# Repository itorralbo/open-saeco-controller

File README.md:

# Open Saeco Controller

Controladora open-source para sustituir la electrónica de la Saeco Incanto HD8911,
placa objetivo 421941308981/01. Proyecto independiente, sin afiliación a Philips/Saeco.

**Rev A: diseño en curso, sin hardware fabricado ni ensayado. Hay 230 VAC. Toda
etapa de potencia es experimental hasta verificación. El firmware actual no
controla cargas.**

## Objetivo
Controlar la máquina sin depender de la electrónica original, inicialmente por USB/web.
Conservar mecánica y cableado solo tras verificar compatibilidad. Se diseñará un frontal
nuevo que reproduzca la posición de los botones y use una pantalla reemplazable.
STM32 se ocupará del control; ESP32, de interfaz y comunicaciones.

## Documentación
- [Arquitectura](docs/architecture.md)
- [Reverse engineering HD8911](docs/HD8911/README.md)
- [Plan de caracterización de la cafetera](docs/HD8911/characterization-plan.md)
- [Mapa I/O preliminar](docs/io-map.md)
- [Diseño preliminar del frontal y pantalla](hardware/front-panel/README.md)
- [Subsistema display y UI (ST7789 + LVGL)](docs/display-ui.md)
- [Decisión de frontal/display (ADR-0001)](docs/adr/0001-front-panel-display-st7789.md)
- [Diseño de la principal](hardware/controller/core-design.md) y
  [su colocación y ruteo](hardware/controller/layout.md)
- [Arquitectura de potencia](hardware/power/power-architecture.md)
- [Abrir y editar los proyectos KiCad](hardware/kicad-workflow.md)
- [Componentes y fabricación JLCPCB](hardware/assembly/README.md)
- [Seguridad](docs/safety.md)
- [Roadmap y validación](docs/roadmap.md)
- [Licencias y fuentes](docs/licensing.md)

## Estructura
```
docs/                 arquitectura, seguridad, ingeniería inversa de la HD8911 y registro de verificación
hardware/controller/  principal completa: esquema, PCB de cuatro capas ruteada, BOM; no fabricable
hardware/front-panel/ frontal: esquema, PCB ruteada y paquete JLCPCB candidato, sin pedir
hardware/assembly/    catálogo de componentes con códigos JLC y stock observado
hardware/power/       diseño de las etapas de red, 24 V, válvula y watchdog
firmware/stm32/       núcleo C portable, sin BSP ni pines
firmware/esp32/       proyecto mínimo ESP-IDF
firmware/common/      contrato de comunicaciones propuesto
recipes/              ejemplo de simulación no ejecutable
sim/                  modelo de las dos placas para el simulador del firmware
tools/                generadores, layout, ruteo y comprobaciones de las dos placas
tests/                pruebas de bloqueo del núcleo
```

## Verificación local
Con Python 3: `python tools/check_scaffold.py`.
Conexiones del frontal: `python tools/check_front_panel.py` (no sustituye ERC).
Núcleo y suministro: `python tools/check_controller_core.py` (no sustituye ERC/DRC).
ERC y netlist nativos, con KiCad 10: `python3 tools/validate_kicad.py`.
Geometría de la PCB principal (condensadores de entrada de los bucks), con el
Python de KiCad desde `tools/`: `check_controller_pcb.py --self-test`.
Coherencia firmware ↔ placas: `python tools/build_board_model.py --check`
([simulador](sim/README.md), [informe](sim/board-report.md)).
Con CMake >= 3.20 y compilador C:
```
cmake -S firmware/stm32 -B build/host
cmake --build build/host --config Debug
ctest --test-dir build/host -C Debug --output-on-failure
```
El build host no produce firmware STM32 flasheable. USB/web, drivers, protocolos y
calibraciones aún no están implementados. Todos los pinouts y niveles eléctricos
sin evidencia permanecen TBD.

El material original de esta base se publica bajo [MIT](LICENSE). Referencias y
materiales de terceros conservan sus derechos; no se redistribuyen en este paquete.

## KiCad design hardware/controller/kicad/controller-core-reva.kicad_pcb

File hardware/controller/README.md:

# Controladora principal

[Diseño de la principal en KiCad](core-design.md): STM32G431RBT6 y
ESP32-S3-WROOM-1U-N8R8 con antena externa U.FL, reset, depuración, UART y USB-C
de servicio. La fuente Mean Well IRM-30-24 va en la propia placa; de sus 24 V
salen el buck de 12 V y, tras él, el de 3,3 V y el corte del frontal. Incluye el
acondicionamiento de NTC, caudalímetro, nivel de agua y tres contactos; un
DRV8876 para el motor del grupo y una etapa low-side para la válvula, cada uno
con su fusible; y las etapas de triac de calentador, bomba y molinillo detrás de
un relé general K701. Un TPS3828 supervisa el STM32 y las puertas AND U602–U604
anulan todas las órdenes de carga y el armado del relé mientras hay reset.

223 posiciones: 214 con MPN y código LCSC, de ellas R415 y R416 sin montar
(DNP); C705, R727, C706 y R728, snubbers RC de los triacs, y C708, supresión del
molinillo, sin montar y sin pieza; J115 y J117 (LEOCO, que JLCPCB no tiene) con MPN y sin código; J111 y
J121, puentes de soldadura. Los tres fusibles de red son Littelfuse 215 de
1500 A a 250 VAC (F702, de 2 A, en pinzas 01110501Z; F701, de 12 A, soldado). J105, J106 y J113 (JP13, JP5 y JP3)
son HR A2506WV, JP8 y JP24 LEOCO 3941P03*000 y 5001P020013, JP17 y JP19 TE RAST 5
1971845-3 y -4 y JP1/JP9 lengüetas TE 63824-1, todas identificadas por el
propietario o casadas con sus fotos. Desde el 2026-10-10 también J107 y J108
(JP14 y JP16, HR A2506WV-02P y -08P) y J109 (JP22, JST ZH B3B-ZR).

La PCB es de cuatro capas, JLC04161H-7628, con planos de GND y 3,3 V solo en el
lado SELV, y está [colocada y ruteada](layout.md) en las posiciones de la placa
original: DRC con todas las severidades sin infracciones ni conexiones abiertas.
La barrera red/SELV de 8 mm es una regla del DRC. Detalle del proyecto en
[kicad-workflow.md](../kicad-workflow.md); reglas y apilado en
[manufacturing.md](manufacturing.md), con el [paquete JLCPCB candidato](fabrication/)
(Gerbers, BOM y CPL, sin pedir); arquitectura de potencia en
[power-architecture.md](../power/power-architecture.md); suministro en
[assembly](../assembly/README.md).

El [contrato del frontal](front-panel-interface.md) fija J104 y los GPIO del
ESP32 para pantalla, botones, UART y USB. Dos divisores permiten leer por ADC los
rails de 12 V y 24 V, y J114 permite medirlos en banco, cada raíl entre dos masas y tras 10 kΩ.

**No es fabricable.** Falta comprobar la placa impresa 1:1 contra la original y
los mazos y el acoplamiento de sus cabeceras, medir la emisión conducida,
medir las cargas y pasar una revisión independiente de aislamiento. Nada está
ensayado. No trasladar pines de una placa de desarrollo al arnés sin verificación.

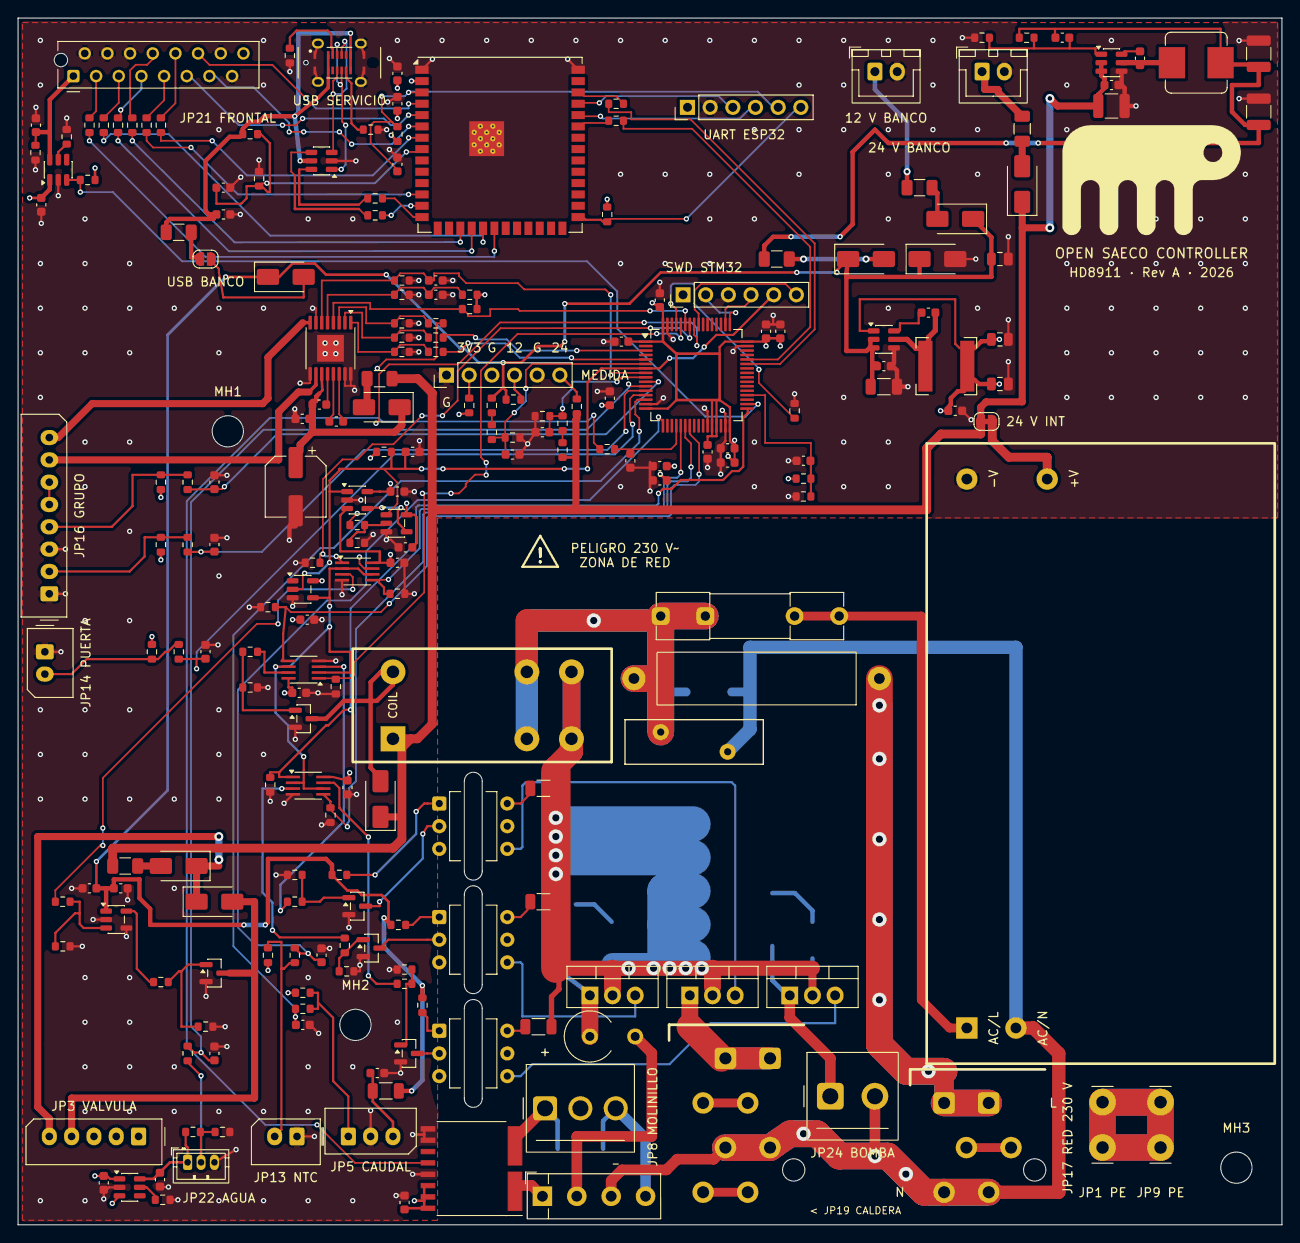
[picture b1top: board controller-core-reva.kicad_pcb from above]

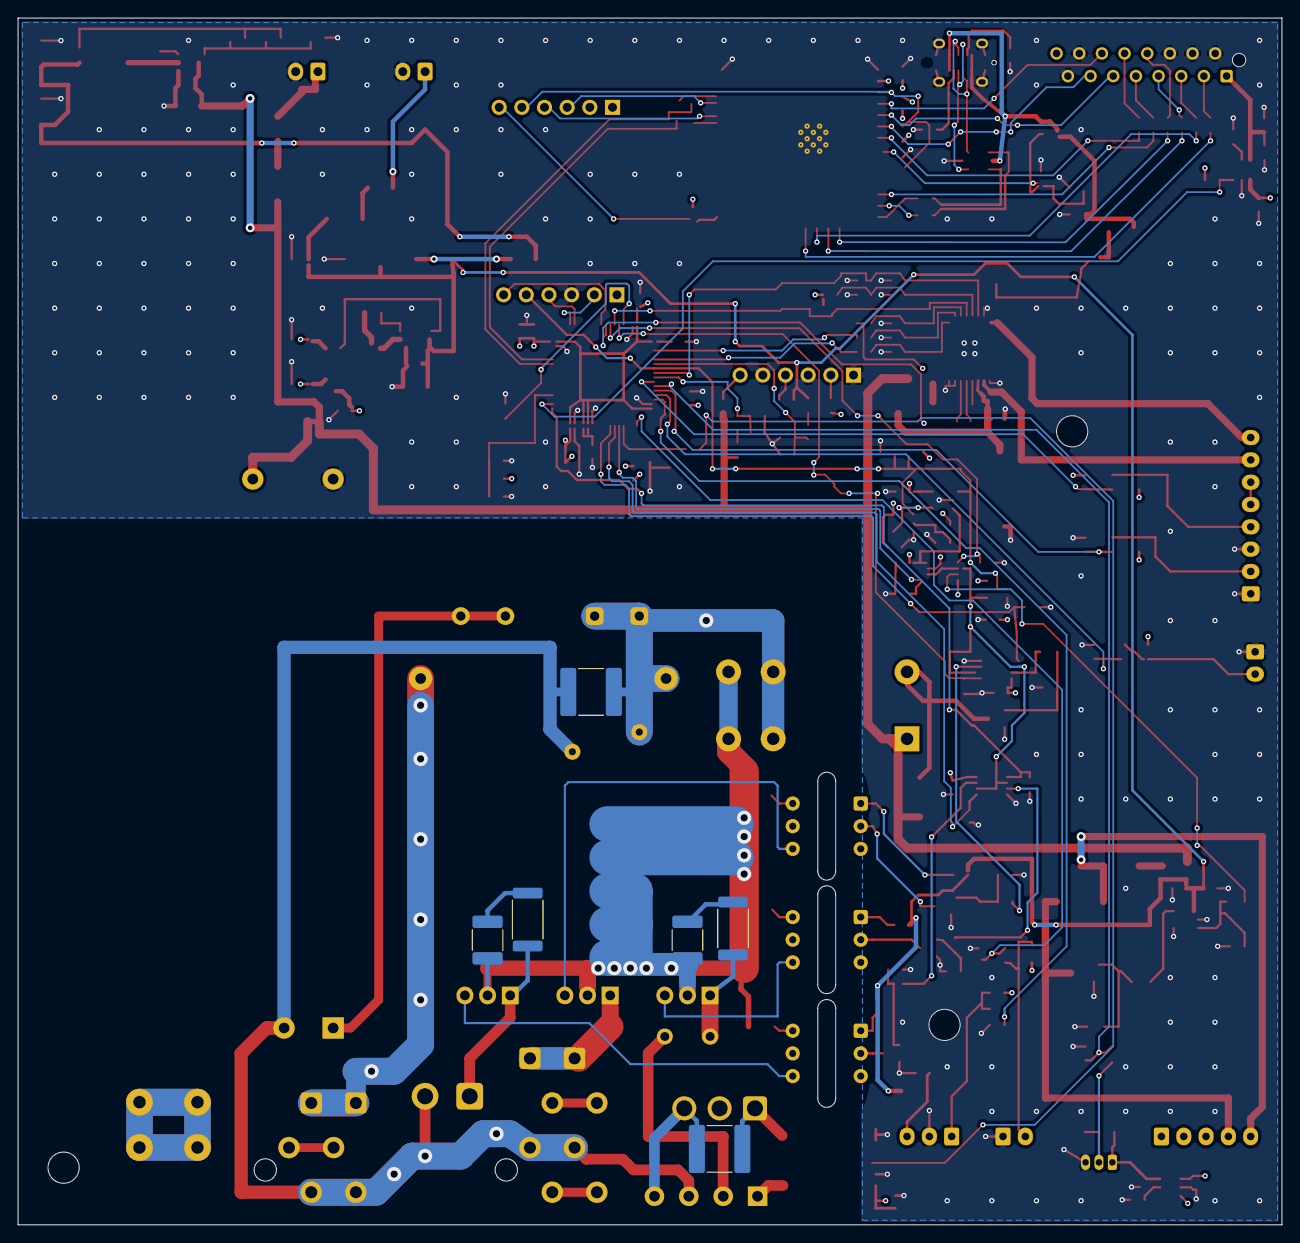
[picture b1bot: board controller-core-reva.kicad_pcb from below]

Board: 4 copper layers, 141.6 x 135.2 mm, 226 parts (6 on the bottom side), 154 nets.

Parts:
BR701: KBP410 / grinder bridge; Diode_Bridge_Vishay_KBPM
C101: 100nF; C_0603_1608Metric
C102: 100nF / VDD16; C_0603_1608Metric
C103: 100nF / VDD32; C_0603_1608Metric
C104: 100nF / VDD48; C_0603_1608Metric
C105: 100nF / VDD64; C_0603_1608Metric
C106: 4.7uF / bulk STM; C_0603_1608Metric
C107: 10nF / VDDA29; C_0603_1608Metric
C108: 1uF / VDDA29; C_0603_1608Metric
C109: 100nF / VREF28; C_0603_1608Metric
C110: 1uF / VREF28; C_0603_1608Metric
C111: 100nF / VBAT1; C_0603_1608Metric
C201: 1uF; C_0603_1608Metric
C202: 100nF / ESP pad2; C_0603_1608Metric
C203: 10uF / ESP pad2; C_0603_1608Metric
C204: 10nF / VBUS sense; C_0603_1608Metric
C205: 1uF / USB VBUS; C_0603_1608Metric
C301: 10uF / 25V input; C_0805_2012Metric
C302: 100nF / input HF; C_0603_1608Metric
C303: 100nF / bootstrap; C_0603_1608Metric
C304, C305: 22uF / 10V output; C_0805_2012Metric
C306: 100nF / output HF; C_0603_1608Metric
C308: 1uF / switch input; C_0603_1608Metric
C309: 10uF / switch output; C_0603_1608Metric
C310: 10uF / 50V input 1210; C_1210_3225Metric
C311: 22uF / 25V output A; C_1210_3225Metric
C312: 22uF / 25V output B; C_1210_3225Metric
C313: 100nF / BST; C_0603_1608Metric
C314: 56pF / feed-forward; C_0603_1608Metric
C315: 10uF / 50V U301 VIN; C_1206_3216Metric
C316: 100nF / U303 VIN HF; C_0603_1608Metric
C401: 100nF / NTC filtro; C_0603_1608Metric
C402: 10nF / FLOW filtro; C_0603_1608Metric
C403: 100nF / DOOR filtro; C_0603_1608Metric
C404: 100nF / PRES filtro; C_0603_1608Metric
C405: 100nF / WORK filtro; C_0603_1608Metric
C406: 10nF / WATER filtro; C_0603_1608Metric
C407: 100nF / GRINDER I filtro; C_0603_1608Metric
C408: 100nF / FLOW VCC; C_0603_1608Metric
C409: 100nF / JP22 switch input; C_0603_1608Metric
C410: 1uF / JP22 VCC; C_0603_1608Metric
C501: 100uF / 35V motor bulk; CP_Elec_6.3x7.7
C502: 100nF / VM local; C_0603_1608Metric
C503: 100nF / VCP-VM; C_0603_1608Metric
C504: 22nF / CPH-CPL; C_0603_1608Metric
C505: 100nF / VREF; C_0603_1608Metric
C506: 10nF / IPROPI; C_0603_1608Metric
C507: 100nF / driver local; C_0603_1608Metric
C508: 1uF / driver local; C_0603_1608Metric
C601: 100nF / supervisor local; C_0603_1608Metric
C602: 100nF / logic local; C_0603_1608Metric
C603: 100nF / arm gate local; C_0603_1608Metric
C604: 100nF / pump gate local; C_0603_1608Metric
C605: 100nF / reset buffer local; C_0603_1608Metric
C606: 100nF / WDI gate local; C_0603_1608Metric
C701: 100nF / 12V ADC; C_0603_1608Metric
C702: 100nF / 24V ADC; C_0603_1608Metric
C703: 100nF / U704 VS; C_0603_1608Metric
C704: 100nF / heatsink NTC; C_0603_1608Metric
C705: RC snubber C / Q704, DNP until PU-03; C_1812_4532Metric
C706: RC snubber C / Q708, DNP until GR-05; C_1812_4532Metric
C707: 56nF X2 / mains input; C_2220_5750Metric
C708: Motor suppression C / JP8, DNP until EMI test; C_2220_5750Metric
D301, D304, D305: SS34; D_SMA
D302: SMAJ15A; D_SMA
D303: SS34 / USB power OR; D_SMA
D306: SS34 / flyback; D_SMA
D307: SS34 / bench OR; D_SMA
D308: SS34 / bench polarity; D_SMA
D701: SS34 / relay flyback; D_SMA
F301, F303, F304: 1A / 72VDC; Fuse_1206_3216Metric
F302: 500mA resettable PTC; Fuse_1206_3216Metric
F305: 1A / 72VDC bench; Fuse_1206_3216Metric
F306: 2A / 72VDC bench; Fuse_1206_3216Metric
F701: T12AH / 250V MAIN; Fuse_Littelfuse_0215_5x20mm_Axial_Horizontal_P27.50mm
F702: T2AH / PSU; Fuseholder_Clip-5x20mm_Littelfuse_111_Inline_P20.00x5.00mm_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
F703: T4AH / 250V grinder; Fuse_Littelfuse_0215_5x20mm_Axial_Vertical_P5.08mm
J101: 12V_ISOLATED_INPUT / JST XH; JST_XH_B2B-XH-A_1x02_P2.50mm_Vertical
J102: STM_SWD / 1x6 2.54mm; PinHeader_1x06_P2.54mm_Vertical
J103: ESP_UART / 1x6 2.54mm; PinHeader_1x06_P2.54mm_Vertical
J104: UI_LINK / WR-MM 16; Wurth_WR-MM_690367181672_2x08_P1.27mm_Vertical
J105: JP13 NTC / 2 vías; HR_A2506WV-02P_1x02_P2.50mm_Vertical
J106: JP5 FLOW ADAPTER / VCC-GND-OC; HR_A2506WV-03P_1x03_P2.50mm_Vertical
J107: JP14 DOOR / A2506WV-02P; HR_A2506WV-02P_1x02_P2.50mm_Vertical
J108: JP16 VISUAL V8..V1 / A2506WV-08P; HR_A2506WV-08P_1x08_P2.50mm_Vertical
J109: JP22 WATER / RED-WHITE-BLACK; JST_ZH_B3B-ZR_1x03_P1.50mm_Vertical
J110: USB-C SERVICE / USB 2.0; USB_C_Receptacle_HRO_TYPE-C-31-D-06_Vertical
J111: USB BENCH POWER / OPEN; SolderJumper-2_P1.3mm_Open_RoundedPad1.0x1.5mm
J112: 24V_ACTUATOR_INPUT / JST XH; JST_XH_B2B-XH-A_1x02_P2.50mm_Vertical
J113: JP3 VALVE / A2506; HR_A2506WV-05P_1x05_P2.50mm_Vertical
J114: POWER PROBE / MEASURE ONLY; PinHeader_1x06_P2.54mm_Vertical
J115: JP8 GRINDER / 320VDC; LEOCO_3941P03_1x03_P3.96mm_Vertical
J116: JP19 HEATER / 1900W 27R5; TE_RAST5_1971845-4_1x04_P5.00mm_Vertical
J117: JP24 PUMP / 230VAC; LEOCO_5001P02_1x02_P5.00mm_Vertical
J118: JP17 MAINS / L-N; TE_RAST5_1971845-3_1x03_P5.00mm_Vertical
J119: JP1 PE TO BOILER; TE_FASTON_63824-1_Tab_6.35mm_Vertical
J120: JP9 PE INPUT; TE_FASTON_63824-1_Tab_6.35mm_Vertical
J121: 24V INTERNAL SELECT / OPEN FOR BENCH; SolderJumper-2_P1.3mm_Bridged_RoundedPad1.0x1.5mm
K701: G5RL-1A-E-HR DC24; Relay_SPST_Omron_G5RL-1A-E-TV8
L301: 3.9uH; L_Bourns-SRN6028
L302: 10uH / 3.5A; L_Bourns_SRP7028A_7.3x6.6mm
MH1, MH2, MH3: PHOTO-DERIVED 3.5mm NPTH; MountingHole_3.5mm
PS701: IRM-30-24; MeanWell_IRM-30_THT
Q501: SI2308A; SOT-23
Q701: BSS138LT1G / relay coil; SOT-23
Q703: BTA24-800BWRG / heater; TO-220-3_Vertical
Q704: BTA24-800BWRG / pump; TO-220-3_Vertical
Q705: BSS138LT1G / heater opto LED; SOT-23
Q706: BSS138LT1G / pump opto LED; SOT-23
Q707: BSS138LT1G / grinder opto LED; SOT-23
Q708: BTA24-800BWRG / grinder; TO-220-3_Vertical
R101, R102, R201, R202: 10k; R_0603_1608Metric
R211, R212, R213, R214, R215, R216, R217, R218, R221, R222: 33; R_0603_1608Metric
R223: 5.1k / CC1 Rd; R_0603_1608Metric
R224: 5.1k / CC2 Rd; R_0603_1608Metric
R225: 100k / VBUS sense top; R_0603_1608Metric
R226: 100k / VBUS sense bottom; R_0603_1608Metric
R301: 100k; R_0603_1608Metric
R302: 330k / 12V FB high; R_0603_1608Metric
R303: 24k / 12V FB low; R_0603_1608Metric
R304: 49.9k / UI ILIM 0.5A; R_0603_1608Metric
R305: 1k / UI discharge; R_0603_1608Metric
R306: 210k / JP22 ILIM 0.13A; R_0603_1608Metric
R401: 4.7k / NTC pull-up; R_0603_1608Metric
R402: 1k / NTC serie; R_0603_1608Metric
R403: 4.7k / FLOW pull-up; R_0603_1608Metric
R404: 1k / FLOW serie; R_0603_1608Metric
R405: 10k / DOOR pull-up; R_0603_1608Metric
R406: 1k / DOOR serie; R_0603_1608Metric
R407: 10k / PRES pull-up; R_0603_1608Metric
R408: 1k / PRES serie; R_0603_1608Metric
R409: 10k / WORK pull-up; R_0603_1608Metric
R410: 1k / WORK serie; R_0603_1608Metric
R411: 1k / WATER serie; R_0603_1608Metric
R412: 1k / GRINDER I serie; R_0603_1608Metric
R413: 390 / FLOW VCC limit; R_1206_3216Metric
R415: 100k / WATER pull-up DNP; R_0603_1608Metric
R416: 100k / WATER pull-down DNP; R_0603_1608Metric
R501: 33 / EN; R_0603_1608Metric
R502: 10k / EN pull-down; R_0603_1608Metric
R503: 33 / PH; R_0603_1608Metric
R504: 10k / PH pull-down; R_0603_1608Metric
R505: 33 / nSLEEP; R_0603_1608Metric
R506: 10k / nSLEEP pull-down; R_0603_1608Metric
R507: 10k / nFAULT pull-up; R_0603_1608Metric
R508: 18k / VREF top; R_0603_1608Metric
R509: 49.9k / VREF bottom; R_0603_1608Metric
R510: 2.4k / IPROPI; R_0603_1608Metric
R511: 33 / IN; R_0603_1608Metric
R512: 10k / IN pull-down; R_0603_1608Metric
R513: 33 / gate; R_0603_1608Metric
R514: 100k / gate pull-down; R_0603_1608Metric
R601: 33 / WDI; R_0603_1608Metric
R602: 1k / kick pull-down; R_0603_1608Metric
R603: 10k / brew arm pull-down; R_0603_1608Metric
R604: 10k / valve pull-down; R_0603_1608Metric
R701: 100k / 12V div A; R_0603_1608Metric
R702: 100k / 12V div B; R_0603_1608Metric
R703: 10k / 12V div low; R_0603_1608Metric
R704: 100k / 24V div A; R_0603_1608Metric
R705: 100k / 24V div B; R_0603_1608Metric
R706: 10k / 24V div low; R_0603_1608Metric
R707, R714, R718: 33 / opto LED gate; R_0603_1608Metric
R708, R715, R719: 100k / opto LED off; R_0603_1608Metric
R709, R716, R720: 1k / opto LED series; R_0603_1608Metric
R710, R712, R721: 390 / gate limit 500V; R_1206_3216Metric
R711: 10k / heater arm pull-down; R_0603_1608Metric
R713: 10k / pump arm pull-down; R_0603_1608Metric
R717: 10k / grinder arm pull-down; R_0603_1608Metric
R722: 10k / mains arm pull-down; R_0603_1608Metric
R723: 10k / J114 3V3 probe; R_0603_1608Metric
R724: 10k / J114 12V probe; R_0603_1608Metric
R725: 10k / J114 24V probe; R_0603_1608Metric
R726: 10k / heatsink NTC pull-up; R_0603_1608Metric
R727: RC snubber R / Q704, DNP until PU-03; R_2512_6332Metric
R728: RC snubber R / Q708, DNP until GR-05; R_2512_6332Metric
R801: 33 / relay gate; R_0603_1608Metric
R802: 100k / relay off; R_0603_1608Metric
RT701: 10k B3380 / heatsink air; R_0603_1608Metric
RV701: S14K275 / 275VAC MOV; RV_Disc_D15.5mm_W5mm_P7.5mm
U101: STM32G431RBT6; LQFP-64_10x10mm_P0.5mm
U201: ESP32-S3-WROOM-1U-N8R8; ESP32-S3-WROOM-1U
U203: USBLC6-2SC6; SOT-23-6
U301: AP63203WU-7; TSOT-23-6
U302: TPS2553DBVR / UI 0.5A limit; SOT-23-6
U303: AP63301WU-7 / 24V to 12V; TSOT-23-6
U304: TPS2553DBVR / JP22 0.13A limit; SOT-23-6
U501: DRV8876PWPR; HTSSOP-16-1EP_4.4x5mm_P0.65mm_EP3x3mm
U502: UCC27517DBVR; SOT-23-5
U601: TPS3828-33DBVR; SOT-23-5
U602, U603, U604: SN74LVC2G08DCTR; SSOP-8_2.95x2.8mm_P0.65mm
U605: SN74LVC1G17DBVR; SOT-23-5
U606: SN74LVC1G132DBVR; SOT-23-5
U701, U702, U703: MOC3083 / zero-cross; DIP-6_W7.62mm_BarrierSlot
U704: TMCS1133B4AQDVGR / grinder current; TI_DVG0010A_SOIC-10W_HV

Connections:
/3V3_CORE: C102.1, C103.1, C104.1, C105.1, C106.1, C107.1, C108.1, C109.1, C110.1, C111.1, C202.1, C203.1, C304.1, C305.1, C306.1, C308.1, C409.1, C601.1, C602.1, C603.1, C604.1, C605.1, C606.1, C703.1, J102.1, J103.1, L301.2, R101.1, R201.1, R202.1, R301.1, R401.1, R403.1, R405.1, R407.1, R409.1, R507.1, R508.1, R723.1, R726.1, U101.1, U101.16, U101.28, U101.29, U101.32, U101.48, U101.64, U201.2, U301.1, U302.1, U304.1, U304.3, U601.3, U601.5, U602.8, U603.8, U604.8, U605.5, U606.5, U704.8, U704.9, U704.10
/3V3_UI: C309.1, J104.1, R305.1, U302.6
/12V_BENCH_FUSED: D307.2, F305.2
/12V_BENCH_RAW: F305.1, J101.1
/12V_FUSED: D301.2, F301.2
/12V_ISO_RAW: C311.1, C312.1, C314.1, F301.1, L302.2, R302.1
/12V_PROTECTED: C301.1, C302.1, C315.1, C507.1, C508.1, D301.1, D302.1, D303.1, D307.1, R413.1, R701.1, R709.1, R716.1, R720.1, R724.1, U301.2, U301.3, U502.1
/24V_ACT_RAW: C310.1, C316.1, D308.1, D701.1, F303.1, F304.1, J121.2, K701.1, R704.1, R725.1, U303.2, U303.3
/24V_BENCH_FUSED: D308.2, F306.2
/24V_BENCH_RAW: F306.1, J112.1
/24V_BREW: C501.1, C502.1, C503.2, D304.1, U501.11
/24V_BREW_FUSED: D304.2, F303.2
/24V_INTERNAL_RAW: J121.1, PS701.4
/24V_VALVE: D305.1, D306.1, J113.5
/24V_VALVE_FUSED: D305.2, F304.2
/BL_RAW: R218.1, U201.7
/BREW_CPH: C504.1, U501.13
/BREW_CPL: C504.2, U501.14
/BREW_CURRENT_ADC: C506.1, R510.1, U101.8, U501.6
/BREW_DIR_DRV: R503.2, R504.1, U501.2
/BREW_DIR_RAW: R503.1, U101.3
/BREW_EN_DRV: R501.2, R502.1, U501.1
/BREW_FAULT_N: R507.2, U101.59, U501.4
/BREW_OUT1: J108.8, U501.8
/BREW_OUT2: J108.7, U501.10
/BREW_PWM_RAW: R501.1, U101.5
/BREW_SLEEP_DRV: R505.2, R506.1, U501.3
/BREW_SLEEP_INTERLOCK: R505.1, U602.7
/BREW_SLEEP_RAW: R603.1, U101.58, U602.1
/BREW_VCP: C503.1, U501.12
/BREW_VREF: C505.1, R508.2, R509.1, U501.5
/BST_NODE: C303.1, U301.6
/BUCK12_BST: C313.1, U303.6
/BUCK12_FB: C314.2, R302.2, R303.1, U303.1
/BUCK12_SW: C313.2, L302.1, U303.5
/BU_BRIDGE: J108.5, J108.6
/BU_PRESENT_N: C404.1, R408.2, U101.10
/BU_PRESENT_RAW: J108.4, R407.2, R408.1
/BU_WORK_N: C405.1, R410.2, U101.12
/BU_WORK_RAW: J108.2, R409.2, R410.1
/CS_RAW: R215.1, U201.18
/DC_RAW: R216.1, U201.17
/DOOR_CLOSED_N: C403.1, R406.2, U101.13
/DOOR_RAW: J107.2, R405.2, R406.1
/ESP_BOOT0: J103.6, R202.2, U201.27
/ESP_DEBUG_RX: J103.4, U201.36
/ESP_DEBUG_TX: J103.3, U201.37
/ESP_EN: C201.1, J103.5, R201.2, U201.3
/ESP_TO_STM: R212.2, U101.44
/ESP_TX_RAW: R212.1, U201.35
/FLOW_RAW: J106.1, R403.2, R404.1
/FLOW_TIM: C402.1, R404.2, U101.14
/FLOW_VCC: C408.1, J106.3, R413.2
/GND_UI: C101.2, C102.2, C103.2, C104.2, C105.2, C106.2, C107.2, C108.2, C109.2, C110.2, C111.2, C201.2, C202.2, C203.2, C204.2, C205.2, C301.2, C302.2, C304.2, C305.2, C306.2, C308.2, C309.2, C310.2, C311.2, C312.2, C315.2, C316.2, C401.2, C402.2, C403.2, C404.2, C405.2, C406.2, C407.2, C408.2, C409.2, C410.2, C501.2, C502.2, C505.2, C506.2, C507.2, C508.2, C601.2, C602.2, C603.2, C604.2, C605.2, C606.2, C701.2, C702.2, C703.2, C704.2, D302.2, J101.2, J102.3, J103.2, J104.2, J104.4, J104.6, J104.14, J104.15, J105.1, J106.2, J107.1, J108.1, J108.3, J109.3, J110.A1, J110.A12, J110.B1, J110.B12, J110.SH, J112.2, J114.1, J114.3, J114.5, PS701.3, Q501.2, Q701.2, Q705.2, Q706.2, Q707.2, R102.2, R223.2, R224.2, R226.2, R303.2, R304.2, R305.2, R306.2, R416.2, R502.2, R504.2, R506.2, R509.2, R510.2, R512.2, R514.2, R602.2, R603.2, R604.2, R703.2, R706.2, R708.2, R711.2, R713.2, R715.2, R717.2, R719.2, R722.2, R802.2, RT701.2, U101.15, U101.27, U101.31, U101.47, U101.63, U201.1, U201.40, U201.41, U203.2, U301.4, U302.2, U303.4, U304.2, U501.7, U501.9, U501.15, U501.16, U501.17, U502.2, U502.4, U601.2, U602.4, U603.4, U604.4, U605.3, U606.3, U704.3, U704.4, U704.7
/GRINDER_AC_FUSED: BR701.2, F703.2
/GRINDER_AC_SWITCHED: F703.1, Q708.1, R728.2
/GRINDER_CURRENT_ADC: C407.1, R412.2, U101.20
/GRINDER_CURRENT_RAW: R412.1, U704.6
/GRINDER_DC_MINUS: BR701.4, C708.2, J115.3
/GRINDER_DC_PLUS: BR701.1, U704.1
/GRINDER_DC_SENSED: C708.1, J115.1, U704.2
/GRINDER_EN_INTERLOCK: R718.1, U604.3
/GRINDER_EN_RAW: R717.1, U101.22, U604.5
/GRINDER_GATE_FEED: R721.2, U703.6
/GRINDER_LED_ANODE: R720.2, U703.1
/GRINDER_LED_GATE: Q707.1, R718.2, R719.1
/GRINDER_LED_RETURN: Q707.3, U703.2
/GRINDER_SNUBBER: C706.2, R728.1
/GRINDER_TRIAC_GATE: Q708.3, U703.4
/HEATER_AC_SWITCHED: J116.1, Q703.1
/HEATER_EN_INTERLOCK: R707.1, U603.3
/HEATER_EN_RAW: R711.1, U101.23, U603.5
/HEATER_GATE_FEED: R710.2, U701.6
/HEATER_LED_ANODE: R709.2, U701.1
/HEATER_LED_GATE: Q705.1, R707.2, R708.1
/HEATER_LED_RETURN: Q705.3, U701.2
/HEATER_TRIAC_GATE: Q703.3, U701.4
/HS_NTC_ADC: C704.1, R726.2, RT701.1, U101.36
/KEY_INT_N: J104.13, U201.6
/KEY_SCL: J104.11, U201.5
/KEY_SDA: J104.12, U201.4
/LCD_BL_PWM: J104.10, R218.2
/LCD_CS_N: J104.7, R215.2
/LCD_DC: J104.8, R216.2
/LCD_MOSI: J104.5, R214.2
/LCD_RST_N: J104.9, R217.2
/LCD_SCLK: J104.3, R213.2
/LOAD_L_ENABLED: C705.1, C706.1, K701.4, K701.5, Q703.2, Q704.2, Q708.2, R710.1, R712.1, R721.1
/MAINS_ARM_RAW: R722.1, U101.60, U603.1
/MAINS_L_FUSED: C707.1, F701.2, F702.1, K701.3, K701.6, RV701.1
/MAINS_L_IN: F701.1, J118.1
/MAINS_N: BR701.3, C707.2, J116.3, J117.2, J118.3, PS701.2, RV701.2
/MAINS_RELAY_EN: R801.1, U603.7
/MAINS_RELAY_GATE: Q701.1, R801.2, R802.1
/MAINS_RELAY_RETURN: D701.2, K701.8, Q701.3
/MOSI_RAW: R214.1, U201.19
/NTC_ADC: C401.1, R402.2, U101.17
/NTC_RAW: J105.2, R401.2, R402.1
/PROBE_3V3: J114.2, R723.2
/PROBE_12V: J114.4, R724.2
/PROBE_24V: J114.6, R725.2
/PROTECTIVE_EARTH: J119.1, J120.1
/PSU_L_FUSED: F702.2, PS701.1
/PUMP_AC_SWITCHED: J117.1, Q704.1, R727.2
/PUMP_EN_INTERLOCK: R714.1, U604.7
/PUMP_EN_RAW: R713.1, U101.33, U604.1
/PUMP_GATE_FEED: R712.2, U702.6
/PUMP_LED_ANODE: R716.2, U702.1
/PUMP_LED_GATE: Q706.1, R714.2, R715.1
/PUMP_LED_RETURN: Q706.3, U702.2
/PUMP_SNUBBER: C705.2, R727.1
/PUMP_TRIAC_GATE: Q704.3, U702.4
/RAIL_12V_ADC: C701.1, R702.2, R703.1, U101.6
/RAIL_12V_DIV: R701.2, R702.1
/RAIL_24V_ADC: C702.1, R705.2, R706.1, U101.9
/RAIL_24V_DIV: R704.2, R705.1
/RST_RAW: R217.1, U201.12
/SCLK_RAW: R213.1, U201.20
/STM_BOOT0: R102.1, U101.61
/STM_NRST: C101.1, J102.5, R101.2, U101.7, U601.1, U605.2, U606.1
/STM_NRST_BUF: U602.2, U602.6, U603.2, U603.6, U604.2, U604.6, U605.4
/STM_SWCLK: J102.4, U101.50
/STM_SWDIO: J102.2, U101.49
/STM_SWO: J102.6, U101.56
/STM_TO_ESP: R211.2, U201.38
/STM_TX_RAW: R211.1, U101.43
/SW_NODE: C303.2, L301.1, U301.5
/UI_ILIM: R304.1, U302.5
/UI_PWR_EN: R301.2, U101.34, U302.3
/USB_BENCH_ENABLE: D303.2, J111.2
/USB_CC1: J110.A5, R223.1
/USB_CC2: J110.B5, R224.1
/USB_DM_DEVICE: R221.1, U203.4
/USB_DM_PORT: J110.A7, J110.B7, U203.3
/USB_DM_RAW: R221.2, U201.13
/USB_DP_DEVICE: R222.1, U203.6
/USB_DP_PORT: J110.A6, J110.B6, U203.1
/USB_DP_RAW: R222.2, U201.14
/USB_VBUS: C205.1, F302.1, J110.A4, J110.A9, J110.B4, J110.B9, R225.1, U203.5
/USB_VBUS_FUSED: F302.2, J111.1
/USB_VBUS_SENSE: C204.1, R225.2, R226.1, U201.8
/VALVE_EN_DRV: R511.2, R512.1, U502.3
/VALVE_EN_INTERLOCK: R511.1, U602.3
/VALVE_EN_RAW: R604.1, U101.21, U602.5
/VALVE_GATE: Q501.1, R513.2, R514.1
/VALVE_GATE_RAW: R513.1, U502.5
/VALVE_RETURN: D306.2, J113.4, Q501.3
/WATCHDOG_KICK: R601.2, R602.1, U606.2
/WATCHDOG_KICK_RAW: R601.1, U101.57
/WATCHDOG_WDI: U601.4, U606.4
/WATER_ILIM: R306.1, U304.5
/WATER_LEVEL: C406.1, R411.2, U101.11
/WATER_RAW: J109.2, R411.1, R415.2, R416.1
/WATER_VCC: C410.1, J109.1, R415.1, U304.6

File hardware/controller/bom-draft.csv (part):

reference,value,footprint,status,manufacturer,mpn,lcsc,jlc_class,pcba_type
U101,STM32G431RBT6,Package_QFP:LQFP-64_10x10mm_P0.5mm,candidate,STMicroelectronics,STM32G431RBT6,C431633,Extended,Economic and Standard
U201,ESP32-S3-WROOM-1U-N8R8,RF_Module:ESP32-S3-WROOM-1U,candidate,Espressif Systems,ESP32-S3-WROOM-1U-N8R8,C2980300,Extended,Standard Only
J101,12V_ISOLATED_INPUT / JST XH,Connector_JST:JST_XH_B2B-XH-A_1x02_P2.50mm_Vertical,candidate,JST,B2B-XH-A(LF)(SN),C158012,Extended,TBD
J102,STM_SWD / 1x6 2.54mm,Connector_PinHeader_2.54mm:PinHeader_1x06_P2.54mm_Vertical,candidate,hanxia,HX PH254-01-06-Z-L11.5 through hole header,C52016393,Extended,Economic and Standard
J103,ESP_UART / 1x6 2.54mm,Connector_PinHeader_2.54mm:PinHeader_1x06_P2.54mm_Vertical,candidate,hanxia,HX PH254-01-06-Z-L11.5 through hole header,C52016393,Extended,Economic and Standard
J104,UI_LINK / WR-MM 16,OpenSaeco:Wurth_WR-MM_690367181672_2x08_P1.27mm_Vertical,owner_identified_supply_pending,Wurth Elektronik,690367181672,C19103863,Extended,TBD
R101,10k,Resistor_SMD:R_0603_1608Metric,candidate,UNI-ROYAL,0603WAF1002T5E,C25804,Basic,Economic and Standard
C101,100nF,Capacitor_SMD:C_0603_1608Metric,candidate,YAGEO,CC0603KRX7R9BB104,C14663,Basic,Economic and Standard
R102,10k,Resistor_SMD:R_0603_1608Metric,candidate,UNI-ROYAL,0603WAF1002T5E,C25804,Basic,Economic and Standard
R201,10k,Resistor_SMD:R_0603_1608Metric,candidate,UNI-ROYAL,0603WAF1002T5E,C25804,Basic,Economic and Standard
C201,1uF,Capacitor_SMD:C_0603_1608Metric,candidate,Samsung Electro-Mechanics,CL10A105KB8NNNC,C15849,Basic,Economic and Standard
R202,10k,Resistor_SMD:R_0603_1608Metric,candidate,UNI-ROYAL,0603WAF1002T5E,C25804,Basic,Economic and Standard
R211,33,Resistor_SMD:R_0603_1608Metric,candidate,UNI-ROYAL,0603WAF330JT5E,C23140,Basic,Economic and Standard
R212,33,Resistor_SMD:R_0603_1608Metric,candidate,UNI-ROYAL,0603WAF330JT5E,C23140,Basic,Economic and Standard
R213,33,Resistor_SMD:R_0603_1608Metric,candidate,UNI-ROYAL,0603WAF330JT5E,C23140,Basic,Economic and Standard
R214,33,Resistor_SMD:R_0603_1608Metric,candidate,UNI-ROYAL,0603WAF330JT5E,C23140,Basic,Economic and Standard
R215,33,Resistor_SMD:R_0603_1608Metric,candidate,UNI-ROYAL,0603WAF330JT5E,C23140,Basic,Economic and Standard
R216,33,Resistor_SMD:R_0603_1608Metric,candidate,UNI-ROYAL,0603WAF330JT5E,C23140,Basic,Economic and Standard
R217,33,Resistor_SMD:R_0603_1608Metric,candidate,UNI-ROYAL,0603WAF330JT5E,C23140,Basic,Economic and Standard
R218,33,Resistor_SMD:R_0603_1608Metric,candidate,UNI-ROYAL,0603WAF330JT5E,C23140,Basic,Economic and Standard
C102,100nF / VDD16,Capacitor_SMD:C_0603_1608Metric,candidate,YAGEO,CC0603KRX7R9BB104,C14663,Basic,Economic and Standard
C103,100nF / VDD32,Capacitor_SMD:C_0603_1608Metric,candidate,YAGEO,CC0603KRX7R9BB104,C14663,Basic,Economic and Standard
C104,100nF / VDD48,Capacitor_SMD:C_0603_1608Metric,candidate,YAGEO,CC0603KRX7R9BB104,C14663,Basic,Economic and Standard
C105,100nF / VDD64,Capacitor_SMD:C_0603_1608Metric,candidate,YAGEO,CC0603KRX7R9BB104,C14663,Basic,Economic and Standard
C106,4.7uF / bulk STM,Capacitor_SMD:C_0603_1608Metric,candidate,Samsung Electro-Mechanics,CL10A475KO8NNNC,C19666,Basic,Economic and Standard
C107,10nF / VDDA29,Capacitor_SMD:C_0603_1608Metric,candidate,FH,0603B103K500NT,C57112,Basic,Economic and Standard
C108,1uF / VDDA29,Capacitor_SMD:C_0603_1608Metric,candidate,Samsung Electro-Mechanics,CL10A105KB8NNNC,C15849,Basic,Economic and Standard
C109,100nF / VREF28,Capacitor_SMD:C_0603_1608Metric,candidate,YAGEO,CC0603KRX7R9BB104,C14663,Basic,Economic and Standard
C110,1uF / VREF28,Capacitor_SMD:C_0603_1608Metric,candidate,Samsung Electro-Mechanics,CL10A105KB8NNNC,C15849,Basic,Economic and Standard
C111,100nF / VBAT1,Capacitor_SMD:C_0603_1608Metric,candidate,YAGEO,CC0603KRX7R9BB104,C14663,Basic,Economic and Standard
C202,100nF / ESP pad2,Capacitor_SMD:C_0603_1608Metric,candidate,YAGEO,CC0603KRX7R9BB104,C14663,Basic,Economic and Standard
C203,10uF / ESP pad2,Capacitor_SMD:C_0603_1608Metric,candidate,Samsung Electro-Mechanics,CL10A106MA8NRNC,C96446,Basic,Economic and Standard
F301,1A / 72VDC,Fuse:Fuse_1206_3216Metric,candidate,prosemi,1206TD-1A,C2838907,Extended,Economic and Standard
D301,SS34,Diode_SMD:D_SMA,candidate,YONGYUTAI,SS34,C2909963,Extended,Economic and Standard
F305,1A / 72VDC bench,Fuse:Fuse_1206_3216Metric,candidate,prosemi,1206TD-1A,C2838907,Extended,Economic and Standard
D307,SS34 / bench OR,Diode_SMD:D_SMA,candidate,YONGYUTAI,SS34,C2909963,Extended,Economic and Standard
D302,SMAJ15A,Diode_SMD:D_SMA,candidate,Littelfuse,SMAJ15A,C148216,Extended,TBD
C301,10uF / 25V input,Capacitor_SMD:C_0805_2012Metric,candidate,Samsung Electro-Mechanics,CL21A106KAYNNNE,C15850,Basic,Economic and Standard
C302,100nF / input HF,Capacitor_SMD:C_0603_1608Metric,candidate,YAGEO,CC0603KRX7R9BB104,C14663,Basic,Economic and Standard
C315,10uF / 50V U301 VIN,Capacitor_SMD:C_1206_3216Metric,candidate,Samsung Electro-Mechanics,CL31B106KBHNNNE,C89632,Extended,Economic and Standard
U301,AP63203WU-7,Package_TO_SOT_SMD:TSOT-23-6,candidate,Diodes Incorporated,AP63203WU-7,C780769,Extended,Economic and Standard
C303,100nF / bootstrap,Capacitor_SMD:C_0603_1608Metric,candidate,YAGEO,CC0603KRX7R9BB104,C14663,Basic,Economic and Standard
L301,3.9uH,Inductor_SMD:L_Bourns-SRN6028,candidate,Bourns,SRN6028C-3R9M,C19947652,Extended,Economic and Standard
C304,22uF / 10V output,Capacitor_SMD:C_0805_2012Metric,candidate,CCTC,TCC0805X5R226M100FT,C380338,Extended,Economic and Standard
C305,22uF / 10V output,Capacitor_SMD:C_0805_2012Metric,candidate,CCTC,TCC0805X5R226M100FT,C380338,Extended,Economic and Standard
C306,100nF / output HF,Capacitor_SMD:C_0603_1608Metric,candidate,YAGEO,CC0603KRX7R9BB104,C14663,Basic,Economic and Standard
U302,TPS2553DBVR / UI 0.5A limit,Package_TO_SOT_SMD:SOT-23-6,candidate,Texas Instruments,TPS2553DBVR,C55266,Extended,Economic and Standard
R301,100k,Resistor_SMD:R_0603_1608Metric,candidate,UNI-ROYAL,0603WAF1003T5E,C25803,Basic,Economic and Standard
R304,49.9k / UI ILIM 0.5A,Resistor_SMD:R_0603_1608Metric,candidate,UNI-ROYAL,0603WAF4992T5E,C23184,Basic,Economic and Standard
R305,1k / UI discharge,Resistor_SMD:R_0603_1608Metric,candidate,UNI-ROYAL,0603WAF1001T5E,C21190,Basic,Economic and Standard
C308,1uF / switch input,Capacitor_SMD:C_0603_1608Metric,candidate,Samsung Electro-Mechanics,CL10A105KB8NNNC,C15849,Basic,Economic and Standard
C309,10uF / switch output,Capacitor_SMD:C_0603_1608Metric,candidate,Samsung Electro-Mechanics,CL10A106MA8NRNC,C96446,Basic,Economic and Standard
J110,USB-C SERVICE / USB 2.0,OpenSaeco:USB_C_Receptacle_HRO_TYPE-C-31-D-06_Vertical,candidate,HRO ELECTRONICS,TYPE-C-31-D-06,C2689964,Extended,TBD
U203,USBLC6-2SC6,Package_TO_SOT_SMD:SOT-23-6,candidate,STMicroelectronics,USBLC6-2SC6,C7519,Extended,Economic and Standard
R221,33,Resistor_SMD:R_0603_1608Metric,candidate,UNI-ROYAL,0603WAF330JT5E,C23140,Basic,Economic and Standard
R222,33,Resistor_SMD:R_0603_1608Metric,candidate,UNI-ROYAL,0603WAF330JT5E,C23140,Basic,Economic and Standard
R223,5.1k / CC1 Rd,Resistor_SMD:R_0603_1608Metric,candidate,UNI-ROYAL,0603WAF5101T5E,C23186,Basic,Economic and Standard
R224,5.1k / CC2 Rd,Resistor_SMD:R_0603_1608Metric,candidate,UNI-ROYAL,0603WAF5101T5E,C23186,Basic,Economic and Standard
R225,100k / VBUS sense top,Resistor_SMD:R_0603_1608Metric,candidate,UNI-ROYAL,0603WAF1003T5E,C25803,Basic,Economic and Standard
R226,100k / VBUS sense bottom,Resistor_SMD:R_0603_1608Metric,candidate,UNI-ROYAL,0603WAF1003T5E,C25803,Basic,Economic and Standard
C204,10nF / VBUS sense,Capacitor_SMD:C_0603_1608Metric,candidate,FH,0603B103K500NT,C57112,Basic,Economic and Standard
C205,1uF / USB VBUS,Capacitor_SMD:C_0603_1608Metric,candidate,Samsung Electro-Mechanics,CL10A105KB8NNNC,C15849,Basic,Economic and Standard
F302,500mA resettable PTC,Fuse:Fuse_1206_3216Metric,candidate,Littelfuse,1206L050YR,C163512,Extended,TBD
J111,USB BENCH POWER / OPEN,Jumper:SolderJumper-2_P1.3mm_Open_RoundedPad1.0x1.5mm,dnp_open_by_default,,,,,
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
